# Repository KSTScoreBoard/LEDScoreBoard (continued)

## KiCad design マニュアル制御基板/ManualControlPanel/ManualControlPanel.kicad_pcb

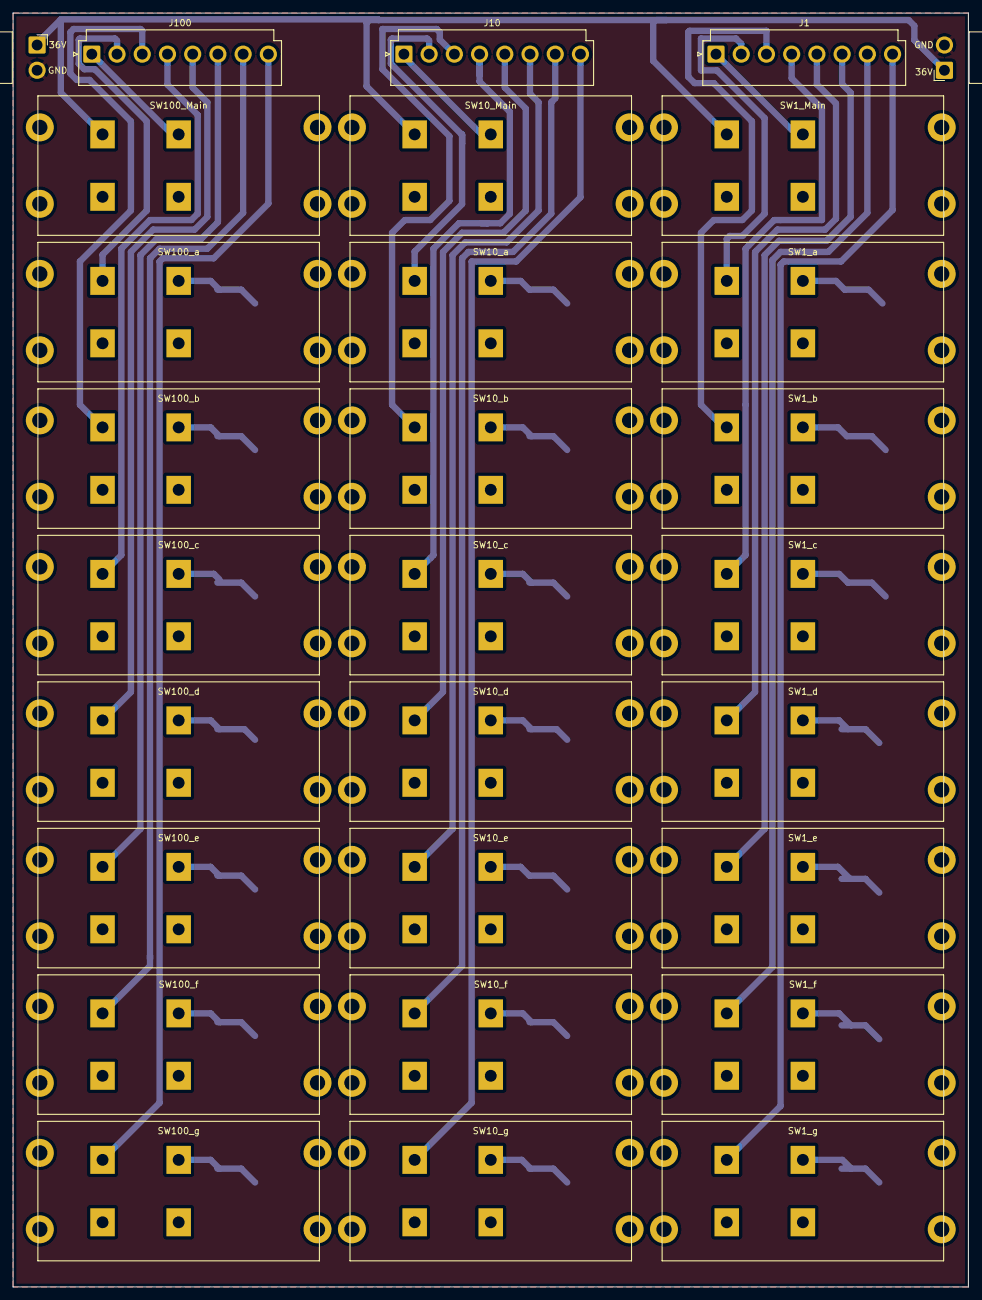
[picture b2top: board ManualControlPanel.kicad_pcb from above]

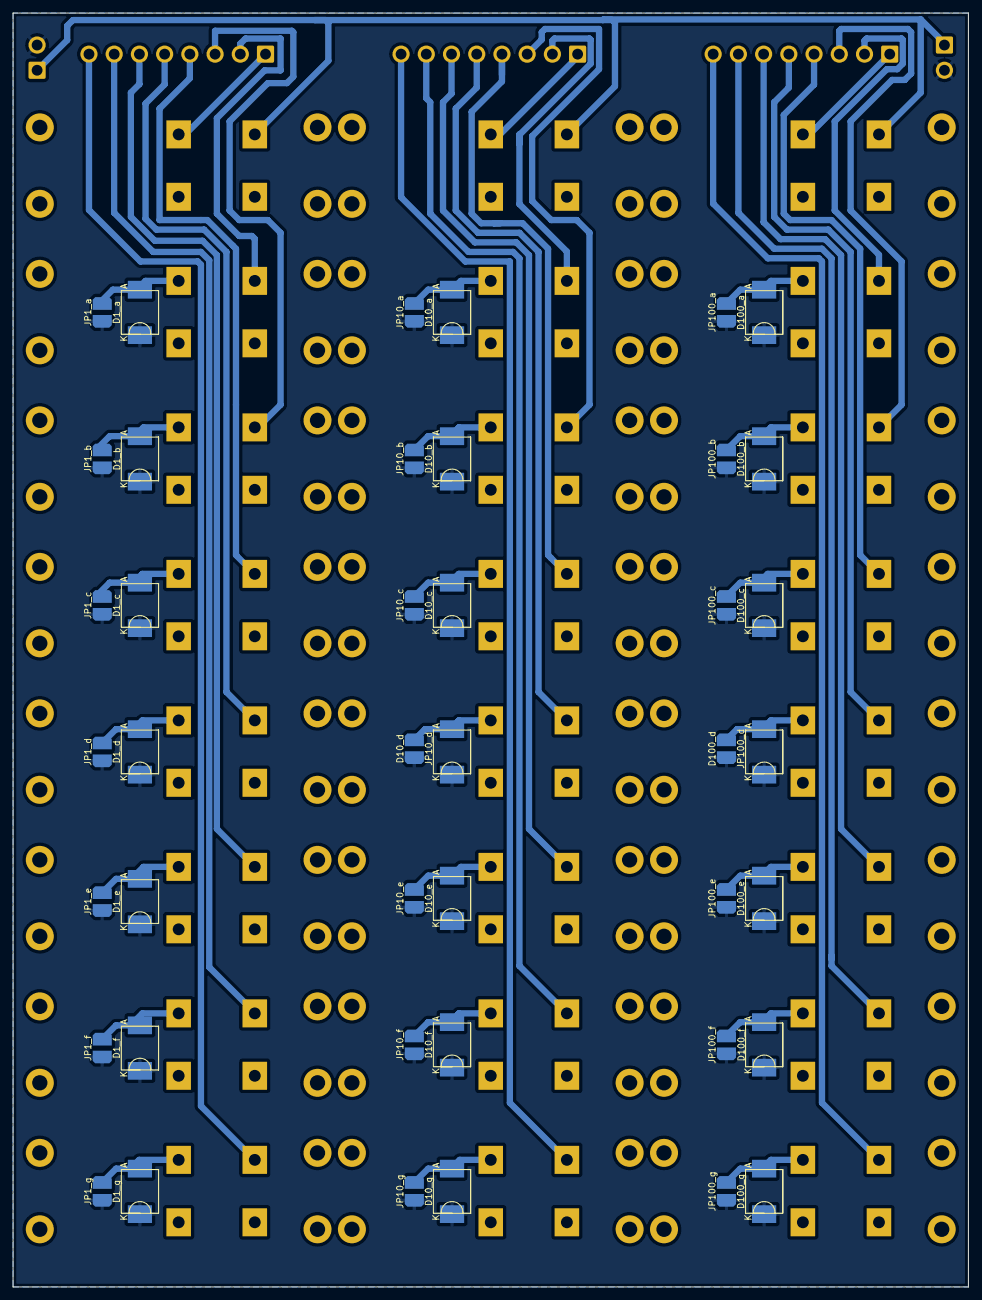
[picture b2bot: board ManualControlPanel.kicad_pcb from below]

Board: 2 copper layers, 150.0 x 200.0 mm, 71 parts (42 on the bottom side), 47 nets.

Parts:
D1_a, D1_b, D1_c, D1_d, D1_e, D1_f, D1_g, D10_a, D10_b, D10_c, D10_d, D10_e, D10_f, D10_g, D100_a, D100_b, D100_c, D100_d, D100_e, D100_f, D100_g: D; NSI50350AST3G
J1, J10, J100: Conn_01x08_Male; JST_VH_B8P-VH-B_1x08_P3.96mm_Vertical
J4, J5: Conn_01x02_Male; JST_VH_B2PS-VH_1x02_P3.96mm_Horizontal
JP1_a, JP1_b, JP1_c, JP1_d, JP1_e, JP1_f, JP1_g, JP10_a, JP10_b, JP10_c, JP10_d, JP10_e, JP10_f, JP10_g, JP100_a, JP100_b, JP100_c, JP100_d, JP100_e, JP100_f, JP100_g: SolderJumper_2_Open; junper
SW1_Main, SW1_a, SW1_b, SW1_c, SW1_d, SW1_e, SW1_f, SW1_g, SW10_Main, SW10_a, SW10_b, SW10_c, SW10_d, SW10_e, SW10_f, SW10_g, SW100_Main, SW100_a, SW100_b, SW100_c, SW100_d, SW100_e, SW100_f, SW100_g: SW_DPST; MS151S

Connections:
+36V: J4.1, J5.1, SW1_Main.1, SW10_Main.1, SW100_Main.1
GND: D1_a.1 (K), D1_b.1 (K), D1_c.1 (K), D1_d.1 (K), D1_e.1 (K), D1_f.1 (K), D1_g.1 (K), D10_a.1 (K), D10_b.1 (K), D10_c.1 (K), D10_d.1 (K), D10_e.1 (K), D10_f.1 (K), D10_g.1 (K), D100_a.1 (K), D100_b.1 (K), D100_c.1 (K), D100_d.1 (K), D100_e.1 (K), D100_f.1 (K), D100_g.1 (K), J4.2, J5.2, JP1_a.1 (A), JP1_b.1 (A), JP1_c.1 (A), JP1_d.1 (A), JP1_e.1 (A), JP1_f.1 (A), JP1_g.1 (A), JP10_a.1 (A), JP10_b.1 (A), JP10_c.1 (A), JP10_d.1 (A), JP10_e.1 (A), JP10_f.1 (A), JP10_g.1 (A), JP100_a.1 (A), JP100_b.1 (A), JP100_c.1 (A), JP100_d.1 (A), JP100_e.1 (A), JP100_f.1 (A), JP100_g.1 (A)
unnamed: D1_a.2 (A), JP1_a.2 (B), SW1_a.2
unnamed: D1_b.2 (A), JP1_b.2 (B), SW1_b.2
unnamed: D1_c.2 (A), JP1_c.2 (B), SW1_c.2
unnamed: D1_d.2 (A), JP1_d.2 (B), SW1_d.2
unnamed: D1_e.2 (A), JP1_e.2 (B), SW1_e.2
unnamed: D1_f.2 (A), JP1_f.2 (B), SW1_f.2
unnamed: D1_g.2 (A), JP1_g.2 (B), SW1_g.2
unnamed: D10_a.2 (A), JP10_a.2 (B), SW10_a.2
unnamed: D10_b.2 (A), JP10_b.2 (B), SW10_b.2
unnamed: D10_c.2 (A), JP10_c.2 (B), SW10_c.2
unnamed: D10_d.2 (A), JP10_d.2 (B), SW10_d.2
unnamed: D10_e.2 (A), JP10_e.2 (B), SW10_e.2
unnamed: D10_f.2 (A), JP10_f.2 (B), SW10_f.2
unnamed: D10_g.2 (A), JP10_g.2 (B), SW10_g.2
unnamed: D100_a.2 (A), JP100_a.2 (B), SW100_a.2
unnamed: D100_b.2 (A), JP100_b.2 (B), SW100_b.2
unnamed: D100_c.2 (A), JP100_c.2 (B), SW100_c.2
unnamed: D100_d.2 (A), JP100_d.2 (B), SW100_d.2
unnamed: D100_e.2 (A), JP100_e.2 (B), SW100_e.2
unnamed: D100_f.2 (A), JP100_f.2 (B), SW100_f.2
unnamed: D100_g.2 (A), JP100_g.2 (B), SW100_g.2
unnamed: J1.1, SW1_Main.2
unnamed: J1.2, SW1_a.1
unnamed: J1.3, SW1_b.1
unnamed: J1.4, SW1_c.1
unnamed: J1.5, SW1_d.1
unnamed: J1.6, SW1_e.1
unnamed: J1.7, SW1_f.1
unnamed: J1.8, SW1_g.1
unnamed: J10.1, SW10_Main.2
unnamed: J10.2, SW10_a.1
unnamed: J10.3, SW10_b.1
unnamed: J10.4, SW10_c.1
unnamed: J10.5, SW10_d.1
unnamed: J10.6, SW10_e.1
unnamed: J10.7, SW10_f.1
unnamed: J10.8, SW10_g.1
unnamed: J100.1, SW100_Main.2
unnamed: J100.2, SW100_a.1
unnamed: J100.3, SW100_b.1
unnamed: J100.4, SW100_c.1
unnamed: J100.5, SW100_d.1
unnamed: J100.6, SW100_e.1
unnamed: J100.7, SW100_f.1
unnamed: J100.8, SW100_g.1

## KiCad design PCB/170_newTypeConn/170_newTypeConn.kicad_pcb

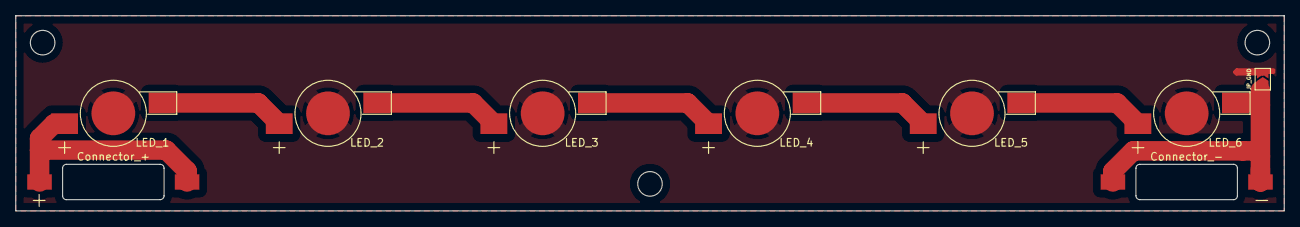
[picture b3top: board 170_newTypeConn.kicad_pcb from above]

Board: 2 copper layers, 165.1 x 25.4 mm, 9 parts (0 on the bottom side), 8 nets.

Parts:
Connector_+: Conn_01x01_Female; BJB46111
Connector_-: Conn_01x01_Female; BJB46111
JP_GND: Jumper_2_Open; SolderJumper-2_P1.3mm_Open_TrianglePad1.0x1.5mm
LED_1, LED_2, LED_3, LED_4, LED_5, LED_6: LED; LED_1W_3W_R8

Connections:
GND: Connector_-.1, JP_GND.1 (A), LED_6.1 (K)
GND1: JP_GND.2 (B), LED_1.3, LED_2.3, LED_3.3, LED_4.3, LED_5.3, LED_6.3
unnamed: LED_1.1 (K), LED_2.2 (A)
unnamed: LED_2.1 (K), LED_3.2 (A)
unnamed: LED_3.1 (K), LED_4.2 (A)
unnamed: LED_4.1 (K), LED_5.2 (A)
unnamed: LED_5.1 (K), LED_6.2 (A)
VDD: Connector_+.1, LED_1.2 (A)

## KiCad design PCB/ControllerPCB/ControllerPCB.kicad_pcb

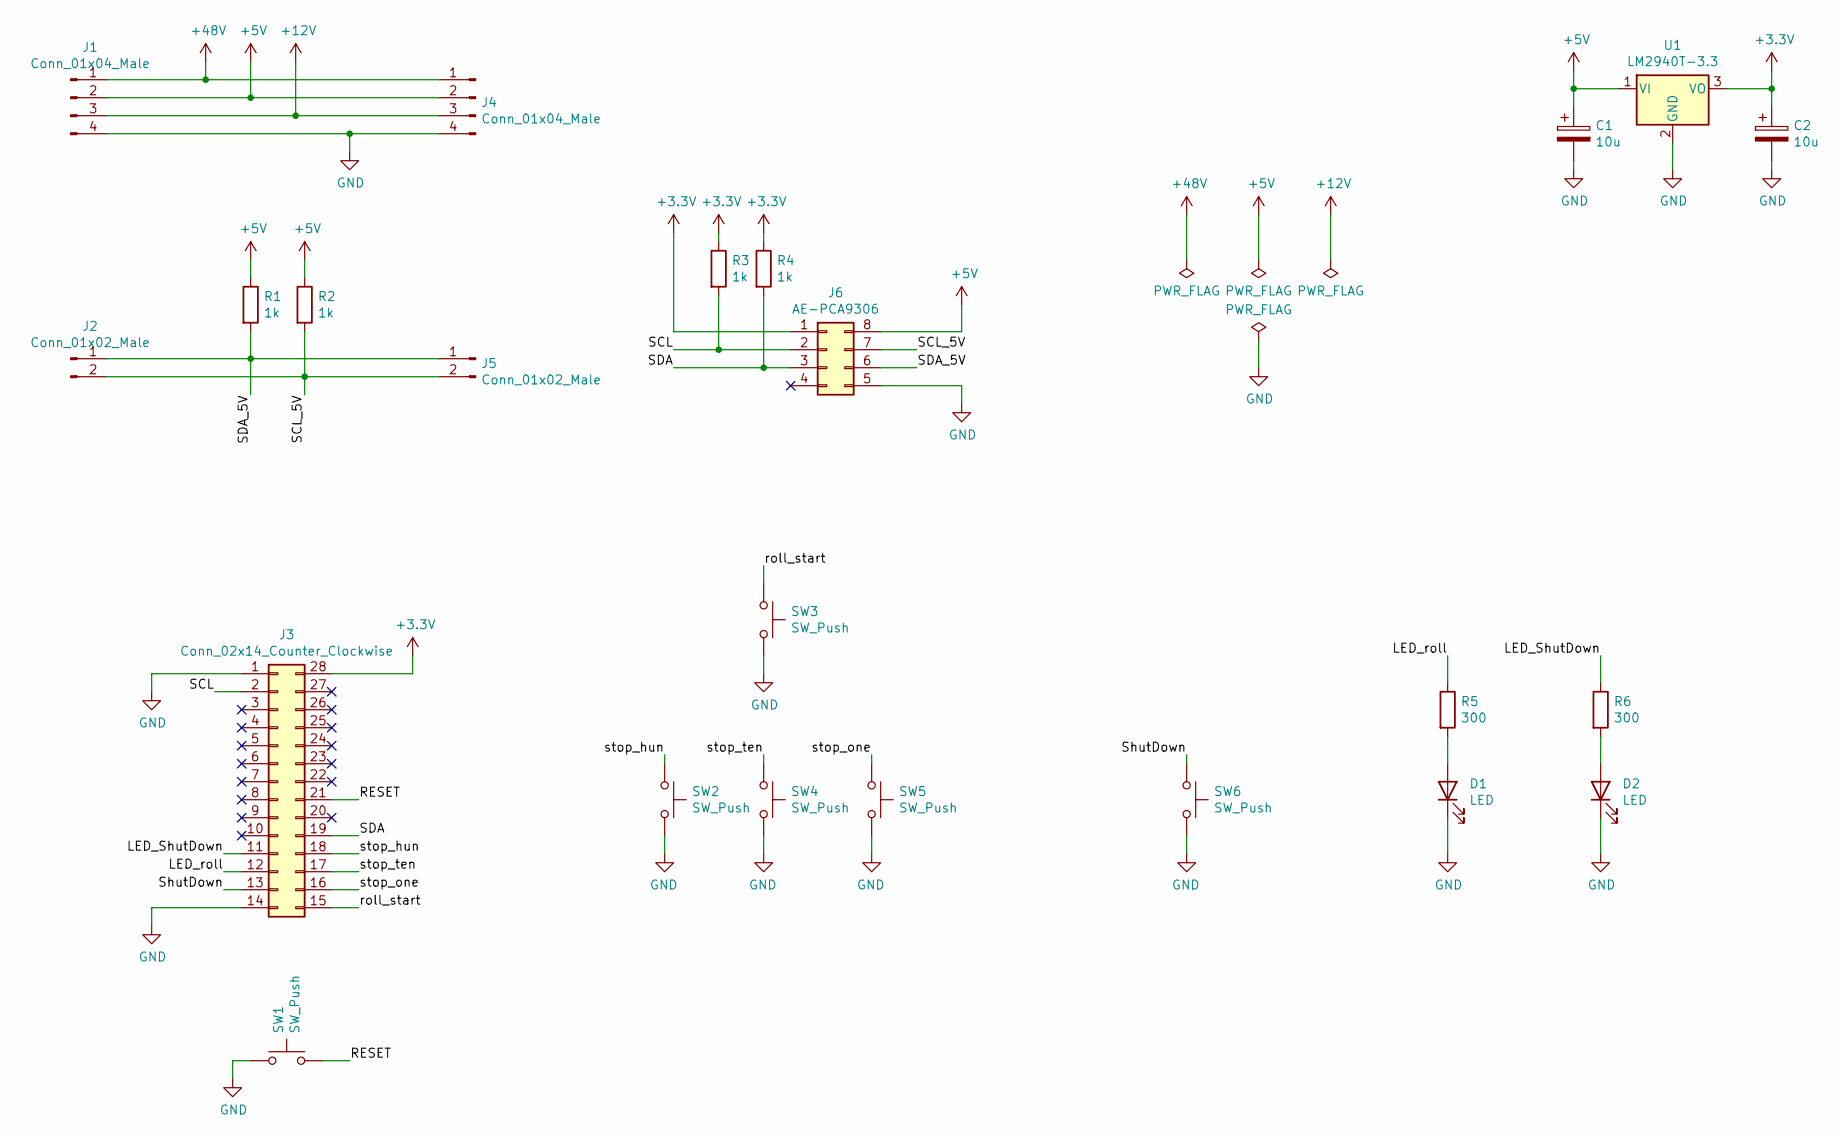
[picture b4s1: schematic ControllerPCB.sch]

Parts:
C1, C2: 10u; CP_Radial_D5.0mm_P2.00mm
D1, D2: LED; LED_0603_1608Metric
J1, J4: Conn_01x04_Male; JST_VH_B4P-VH_1x04_P3.96mm_Vertical
J2, J5: Conn_01x02_Male; JST_XH_B2B-XH-A_1x02_P2.50mm_Vertical
J3: Conn_02x14_Counter_Clockwise; DIP-28_W15.24mm
J6: AE-PCA9306; DIP-8_W7.62mm
R1, R2, R3, R4: 1k; R_0603_1608Metric
R5, R6: 300; R_0603_1608Metric
SW1, SW2, SW3, SW4, SW5, SW6: SW_Push; SW_PUSH_6mm_H5mm
U1: LM2940T-3.3; TO-220-3_Vertical

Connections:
+3V3: C2.1, J3.28, J6.1, R3.1, R4.1, U1.3 (VO)
+5V: C1.1, J1.2, J4.2, J6.8, R1.1, R2.1, U1.1 (VI)
+12V: J1.3, J4.3
+48V: J1.1, J4.1
/LED_ShutDown: J3.11, R6.1
/LED_roll: J3.12, R5.1
/RESET: J3.21, SW1.2
/SCL: J3.2, J6.2, R3.2
/SCL_5V: J2.2, J5.2, J6.7, R2.2
/SDA: J3.19, J6.3, R4.2
/SDA_5V: J2.1, J5.1, J6.6, R1.2
/ShutDown: J3.13, SW6.1
/roll_start: J3.15, SW3.1
/stop_hun: J3.18, SW2.1
/stop_one: J3.16, SW5.1
/stop_ten: J3.17, SW4.1
GND: C1.2, C2.2, D1.1 (K), D2.1 (K), J1.4, J3.1, J3.14, J4.4, J6.5, SW1.1, SW2.2, SW3.2, SW4.2, SW5.2, SW6.2, U1.2 (GND)
unnamed: D1.2 (A), R5.2
unnamed: D2.2 (A), R6.2

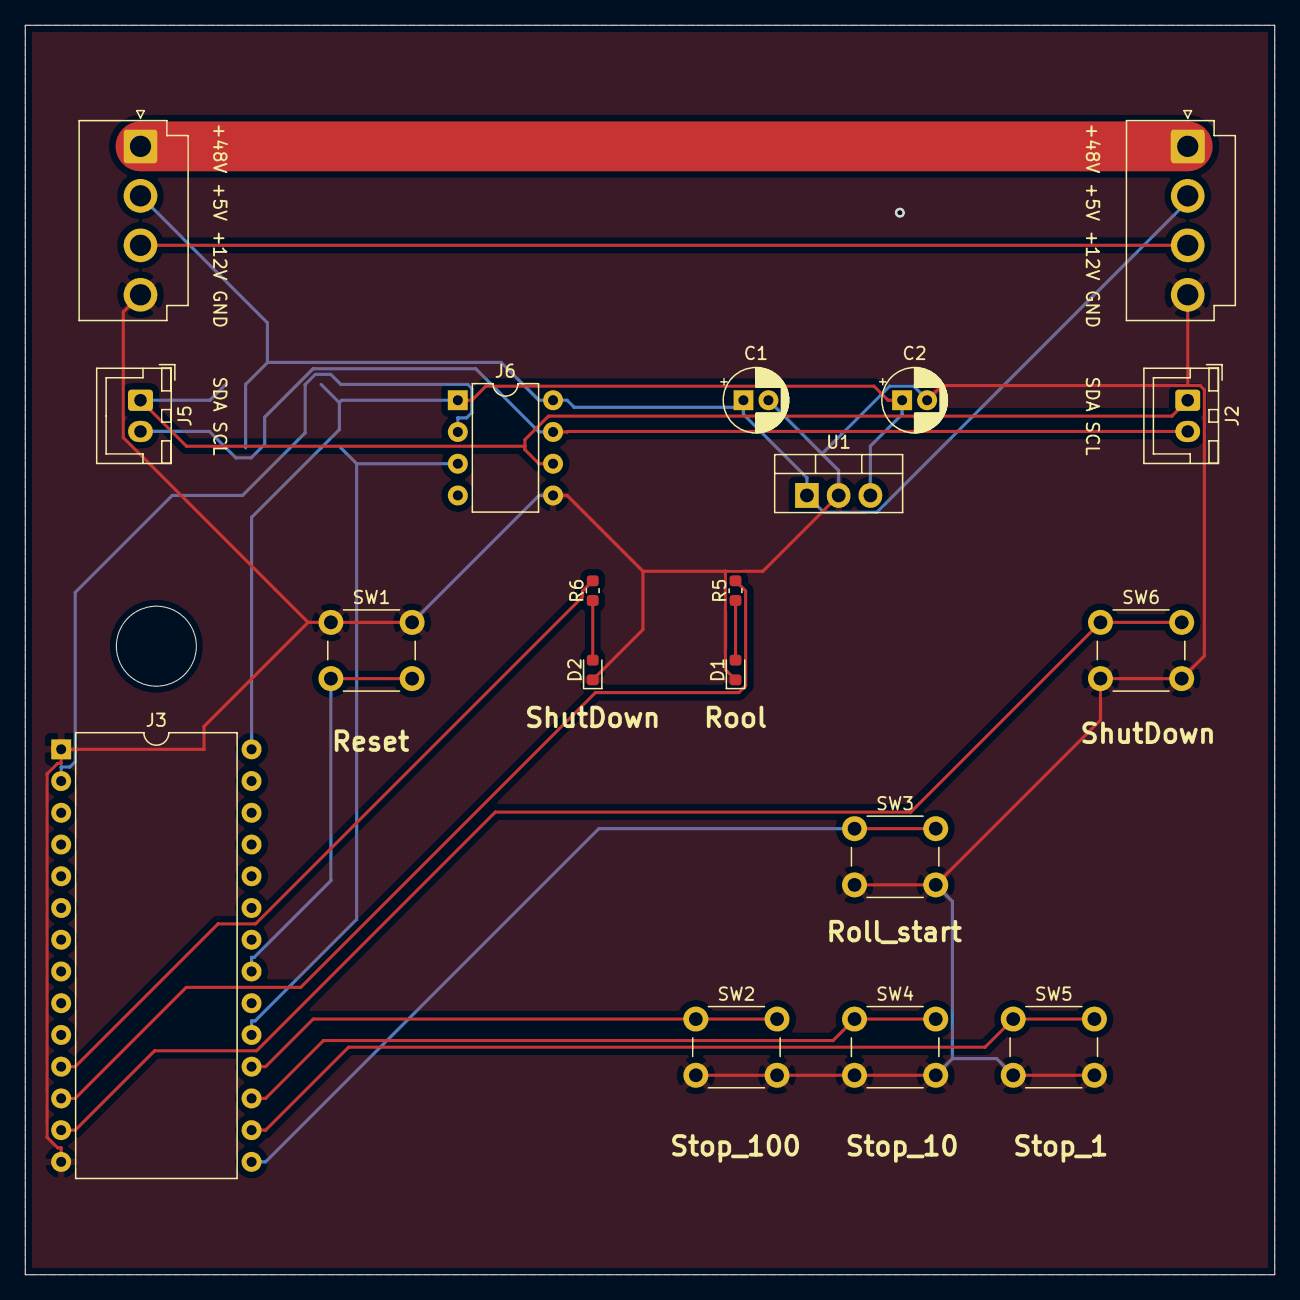
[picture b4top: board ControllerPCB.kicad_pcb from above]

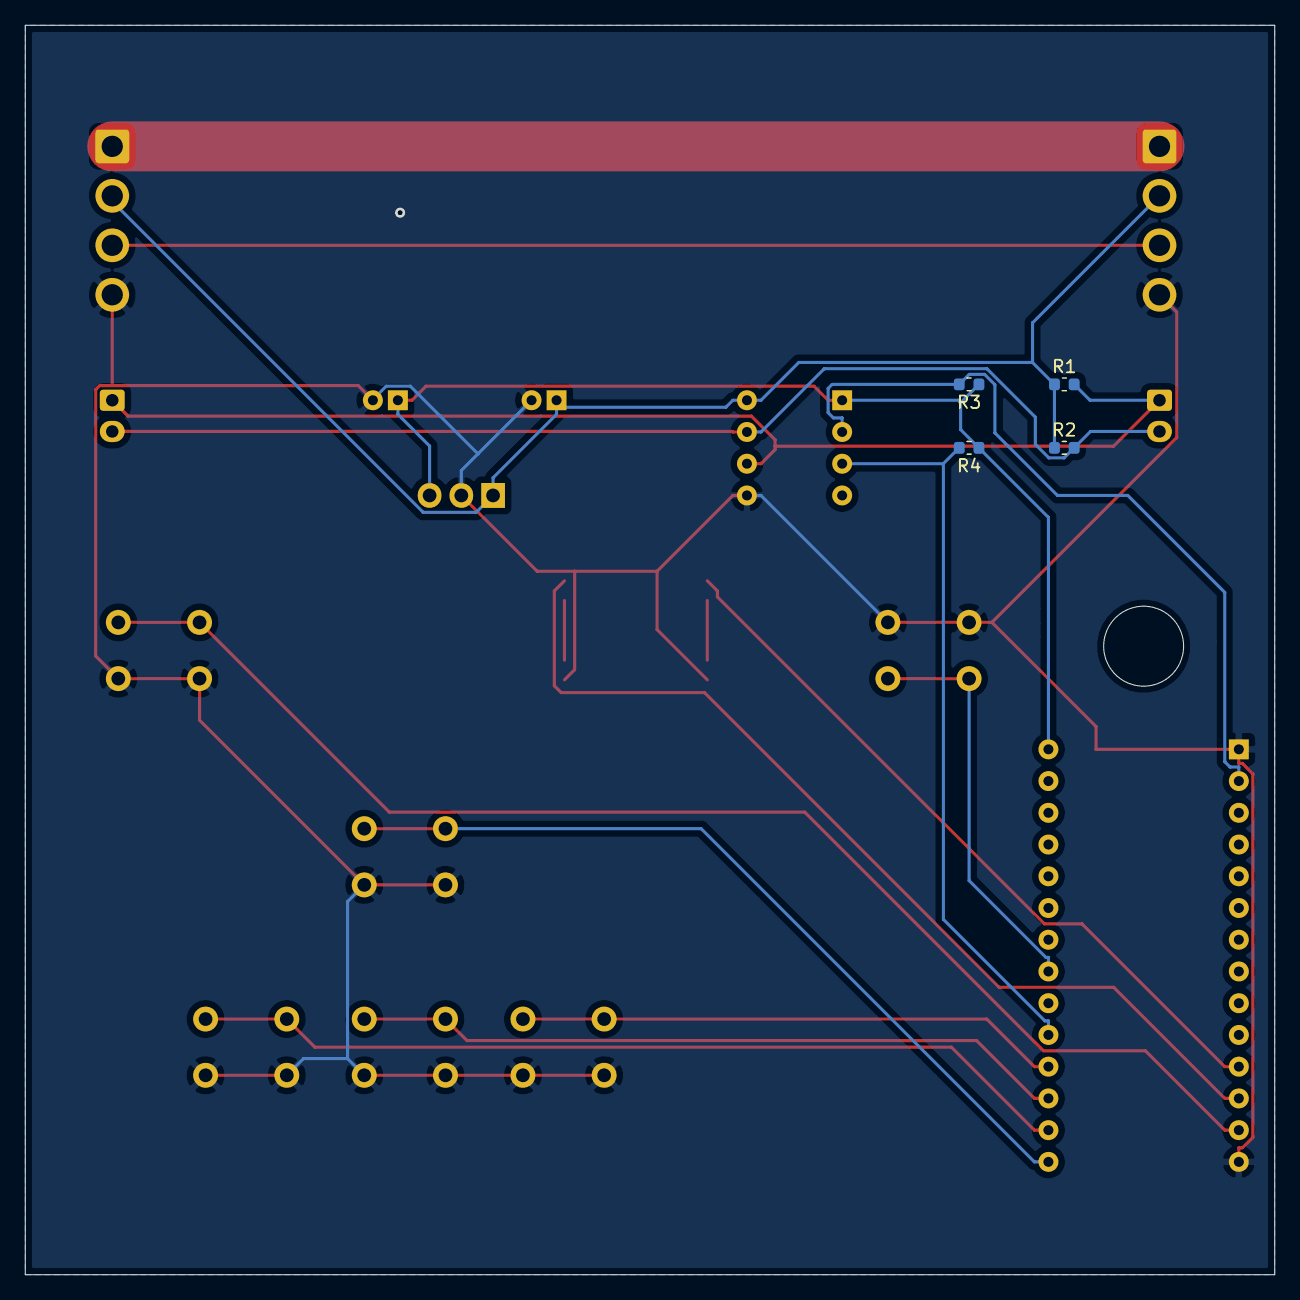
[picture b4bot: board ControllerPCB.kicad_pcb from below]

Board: 2 copper layers, 100.0 x 100.0 mm, 23 parts (4 on the bottom side), 19 nets.

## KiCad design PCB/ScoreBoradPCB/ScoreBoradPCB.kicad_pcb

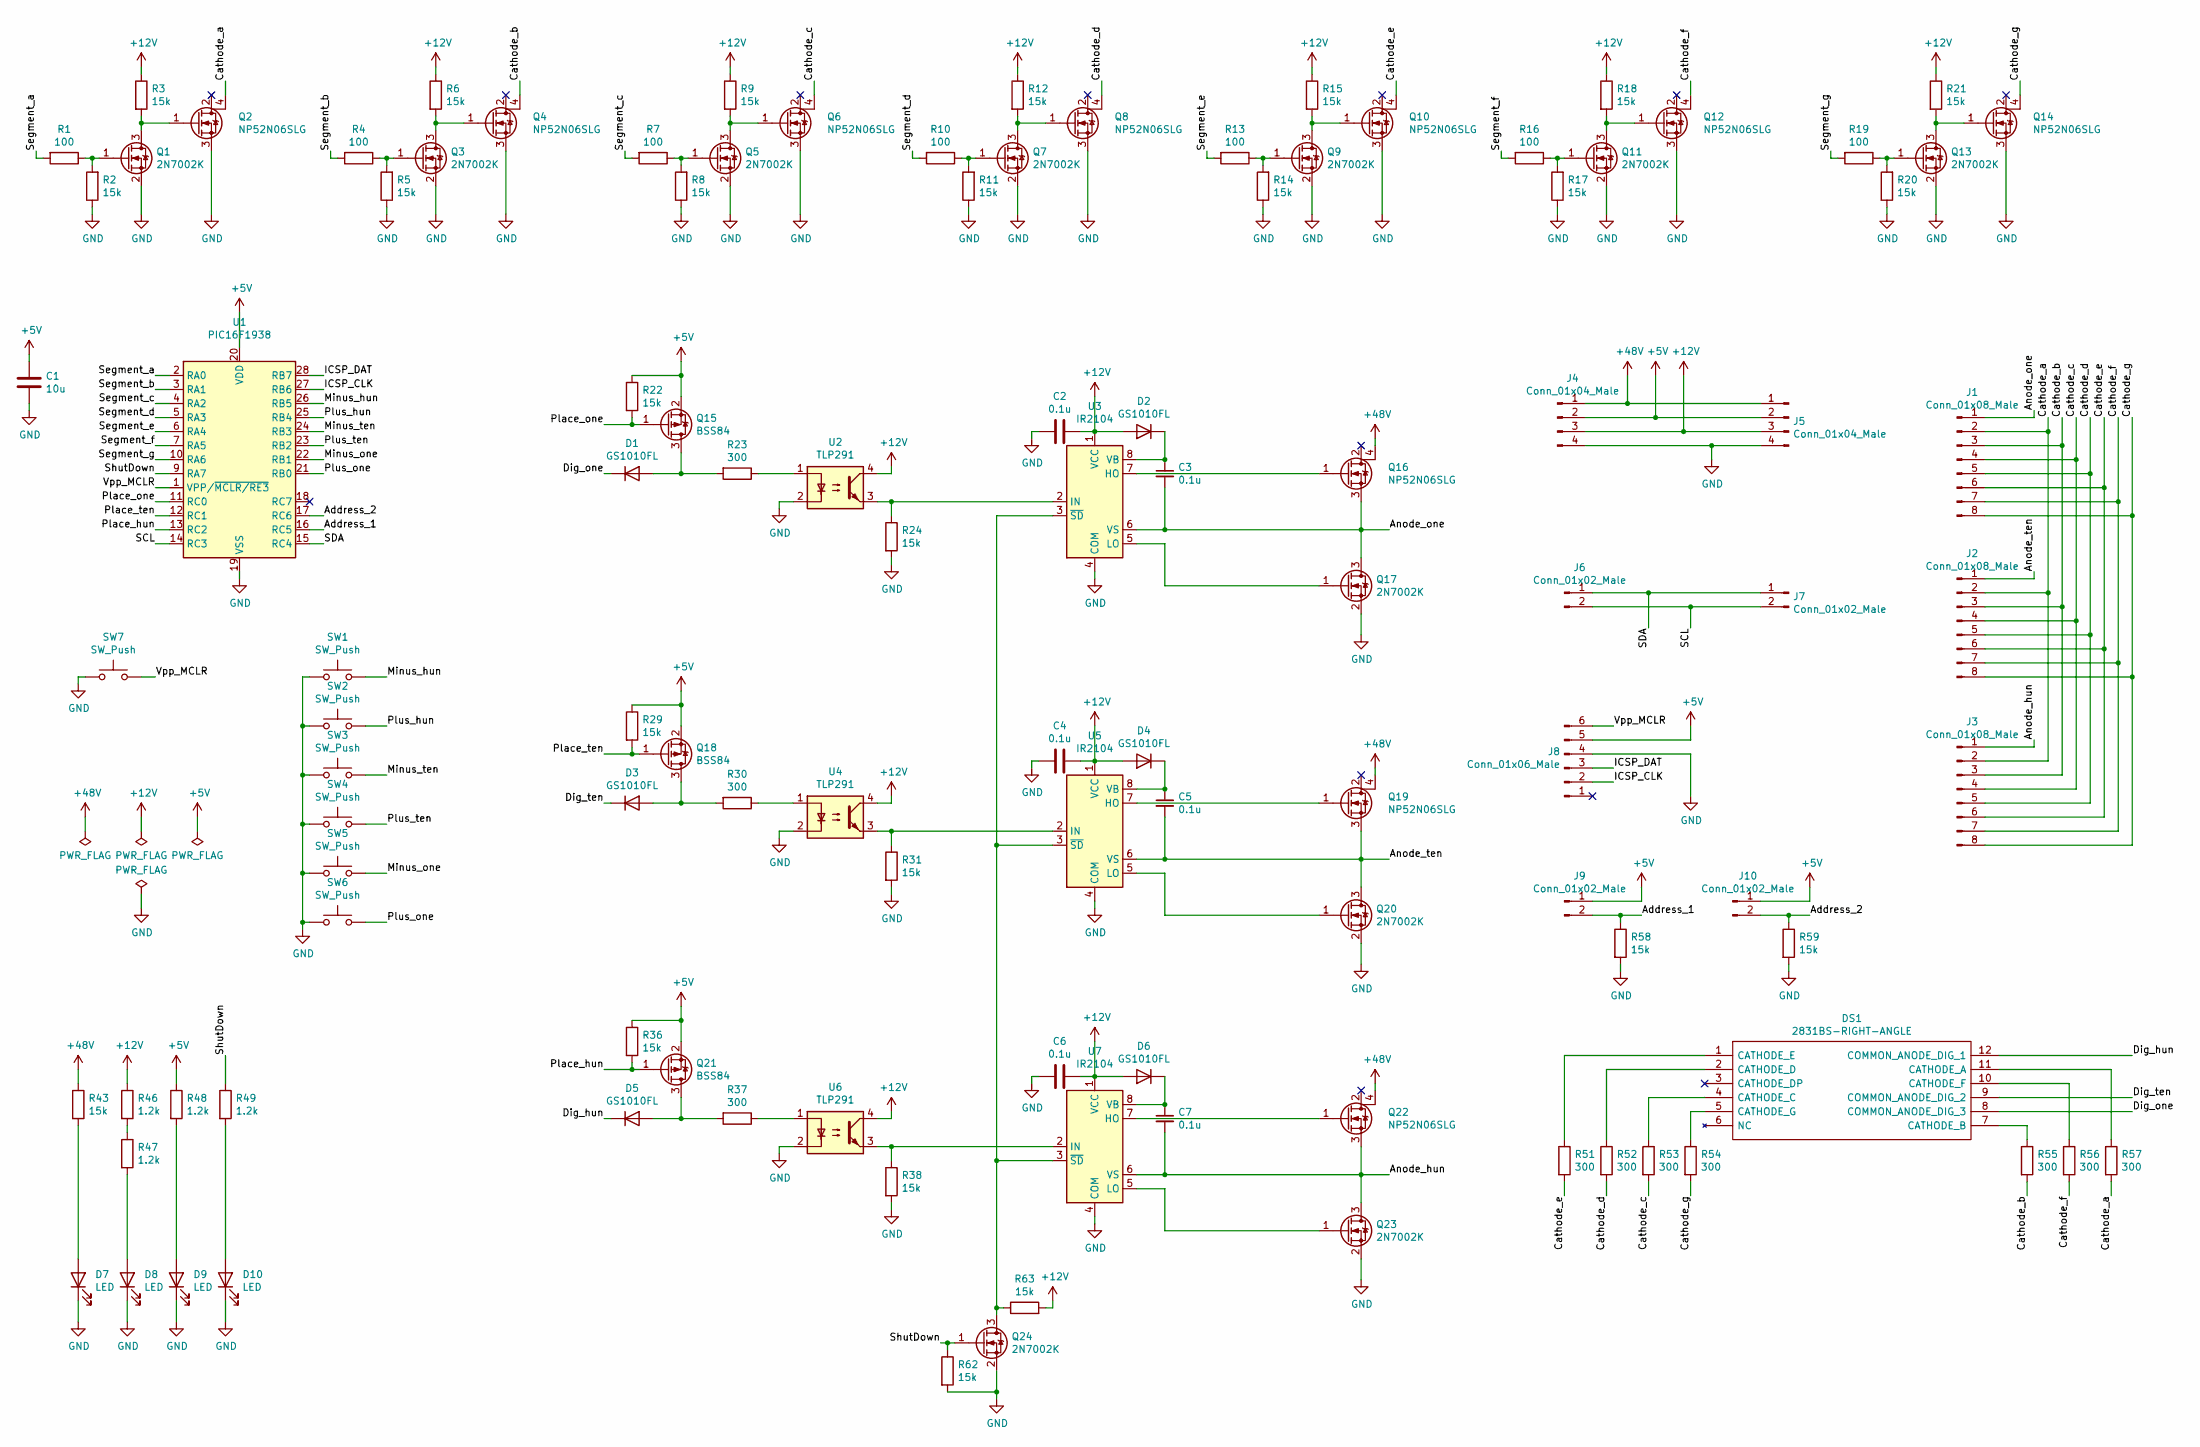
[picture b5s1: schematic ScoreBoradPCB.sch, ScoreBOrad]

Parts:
C1: 10u; C_0603_1608Metric
C2, C3, C4, C5, C6, C7: 0.1u; C_0603_1608Metric
D1, D2, D3, D4, D5, D6: GS1010FL; D_SOD-123F
D7, D8, D9, D10: LED; LED_0603_1608Metric
DS1: 2831BS-RIGHT-ANGLE; DIPS762W45P254L2253H610Q12N; Manufacturer_Part_Number 2831BS-RIGHT-ANGLE
J1, J2, J3: Conn_01x08_Male; JST_VH_B8P-VH_1x08_P3.96mm_Vertical
J4, J5: Conn_01x04_Male; JST_VH_B4P-VH_1x04_P3.96mm_Vertical
J6, J7: Conn_01x02_Male; JST_XH_B2B-XH-A_1x02_P2.50mm_Vertical
J8: Conn_01x06_Male; PinHeader_1x06_P2.54mm_Horizontal
J9, J10: Conn_01x02_Male; PinHeader_1x02_P2.54mm_Vertical
Q1, Q3, Q5, Q7, Q9, Q11, Q13, Q17, Q20, Q23, Q24: 2N7002K; SOT-23
Q2, Q4, Q6, Q8, Q10, Q12, Q14, Q16, Q19, Q22: NP52N06SLG; TO-252-3_TabPin4
Q15, Q18, Q21: BSS84; SOT-23
R1, R4, R7, R10, R13, R16, R19: 100; R_0603_1608Metric
R2, R3, R5, R6, R8, R9, R11, R12, R14, R15, R17, R18, R20, R21, R22, R24, R29, R31, R36, R38, R43, R58, R59, R62, R63: 15k; R_0603_1608Metric
R23, R30, R37, R51, R52, R53, R54, R55, R56, R57: 300; R_0603_1608Metric
R46, R47, R48, R49: 1.2k; R_0603_1608Metric
SW1, SW2, SW3, SW4, SW5, SW6, SW7: SW_Push; SW_PUSH_6mm_H5mm
U1: PIC16F1938; DIP-28_W7.62mm_Socket
U2, U4, U6: TLP291; SOIC-4_4.55x2.6mm_P1.27mm
U3, U5, U7: IR2104; SOIC-8_3.9x4.9mm_P1.27mm

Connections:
+5V: C1.1, J4.2, J5.2, J8.5, J9.1, J10.1, Q15.2 (S), Q18.2 (S), Q21.2 (S), R22.1, R29.1, R36.1, R48.1, U1.20 (VDD); also elsewhere on the board
+12V: C2.1, C4.1, C6.1, D2.2 (A), D4.2 (A), D6.2 (A), J4.3, J5.3, R3.1, R6.1, R9.1, R12.1, R15.1, R18.1, R21.1, R46.1, R63.2, U2.4, U3.1 (VCC), U4.4, U5.1 (VCC), U6.4, U7.1 (VCC)
+48V: J4.1, J5.1, Q16.4 (D), Q19.4 (D), Q22.4 (D), R43.1
/Address_1: J9.2, R58.1, U1.16 (RC5)
/Address_2: J10.2, R59.1, U1.17 (RC6)
/Anode_hun: C7.2, J3.1, Q22.3 (S), Q23.3 (D), U7.6 (VS); also elsewhere on the board
/Anode_one: C3.2, J1.1, Q16.3 (S), Q17.3 (D), U3.6 (VS); also elsewhere on the board
/Anode_ten: C5.2, J2.1, Q19.3 (S), Q20.3 (D), U5.6 (VS); also elsewhere on the board
/Cathode_a: J1.2, J2.2, J3.2, Q2.4 (D), R57.2
/Cathode_b: J1.3, J2.3, J3.3, Q4.4 (D), R55.2
/Cathode_c: J1.4, J2.4, J3.4, Q6.4 (D), R53.2
/Cathode_d: J1.5, J2.5, J3.5, Q8.4 (D), R52.2
/Cathode_e: J1.6, J2.6, J3.6, Q10.4 (D), R51.2
/Cathode_f: J1.7, J2.7, J3.7, Q12.4 (D), R56.2
/Cathode_g: J1.8, J2.8, J3.8, Q14.4 (D), R54.2
/Dig_hun: D5.1 (K), DS1.12 (COMMON_ANODE_DIG_1)
/Dig_one: D1.1 (K), DS1.8 (COMMON_ANODE_DIG_3)
/Dig_ten: D3.1 (K), DS1.9 (COMMON_ANODE_DIG_2)
/ICSP_CLK: J8.2, U1.27 (RB6)
/ICSP_DAT: J8.3, U1.28 (RB7)
/Minus_hun: SW1.2, U1.26 (RB5)
/Minus_one: SW5.2, U1.22 (RB1)
/Minus_ten: SW3.2, U1.24 (RB3)
/Place_hun: Q21.1 (G), R36.2, U1.13 (RC2)
/Place_one: Q15.1 (G), R22.2, U1.11 (RC0)
/Place_ten: Q18.1 (G), R29.2, U1.12 (RC1)
/Plus_hun: SW2.2, U1.25 (RB4)
/Plus_one: SW6.2, U1.21 (RB0)
/Plus_ten: SW4.2, U1.23 (RB2)
/SCL: J6.2, J7.2, U1.14 (RC3); also elsewhere on the board
/SDA: J6.1, J7.1, U1.15 (RC4); also elsewhere on the board
/Segment_a: R1.2, U1.2 (RA0)
/Segment_b: R4.2, U1.3 (RA1)
/Segment_c: R7.2, U1.4 (RA2)
/Segment_d: R10.2, U1.5 (RA3)
/Segment_e: R13.2, U1.6 (RA4)
/Segment_f: R16.2, U1.7 (RA5)
/Segment_g: R19.2, U1.10 (RA6)
/ShutDown: Q24.1 (G), R49.1, R62.1, U1.9 (RA7)
/Vpp_MCLR: J8.6, SW7.2, U1.1 (VPP/~MCLR/RE3)
GND: C1.2, C2.2, C4.2, C6.2, D7.1 (K), D8.1 (K), D9.1 (K), D10.1 (K), J4.4, J5.4, J8.4, Q1.2 (S), Q2.3 (S), Q3.2 (S), Q4.3 (S), Q5.2 (S), Q6.3 (S), Q7.2 (S), Q8.3 (S), Q9.2 (S), Q10.3 (S), Q11.2 (S), Q12.3 (S), Q13.2 (S), Q14.3 (S), Q17.2 (S), Q20.2 (S), Q23.2 (S), Q24.2 (S), R2.1, R5.1, R8.1, R11.1, R14.1, R17.1, R20.1, R24.2, R31.2, R38.2, R58.2, R59.2, R62.2, SW1.1, SW2.1, SW3.1, SW4.1, SW5.1, SW6.1, SW7.1, U1.8 (VSS), U1.19 (VSS), U2.2, U3.4 (COM), U4.2, U5.4 (COM), U6.2, U7.4 (COM); also elsewhere on the board
unnamed: C3.1, D2.1 (K), U3.8 (VB)
unnamed: C5.1, D4.1 (K), U5.8 (VB)
unnamed: C7.1, D6.1 (K), U7.8 (VB)
unnamed: D1.2 (A), Q15.3 (D), R23.2
unnamed: D3.2 (A), Q18.3 (D), R30.2
unnamed: D5.2 (A), Q21.3 (D), R37.2
unnamed: D8.2 (A), R47.2
unnamed: D9.2 (A), R48.2
unnamed: D10.2 (A), R49.2
unnamed: DS1.1 (CATHODE_E), R51.1
unnamed: DS1.2 (CATHODE_D), R52.1
unnamed: DS1.4 (CATHODE_C), R53.1
unnamed: DS1.5 (CATHODE_G), R54.1
unnamed: DS1.7 (CATHODE_B), R55.1
unnamed: DS1.10 (CATHODE_F), R56.1
unnamed: DS1.11 (CATHODE_A), R57.1
unnamed: Q1.1 (G), R1.1, R2.2
unnamed: Q1.3 (D), Q2.1 (G), R3.2
unnamed: Q3.1 (G), R4.1, R5.2
unnamed: Q3.3 (D), Q4.1 (G), R6.2
unnamed: Q5.1 (G), R7.1, R8.2
unnamed: Q5.3 (D), Q6.1 (G), R9.2
unnamed: Q7.1 (G), R10.1, R11.2
unnamed: Q7.3 (D), Q8.1 (G), R12.2
unnamed: Q9.1 (G), R13.1, R14.2
unnamed: Q9.3 (D), Q10.1 (G), R15.2
unnamed: Q11.1 (G), R16.1, R17.2
unnamed: Q11.3 (D), Q12.1 (G), R18.2
unnamed: Q13.1 (G), R19.1, R20.2
unnamed: Q13.3 (D), Q14.1 (G), R21.2
unnamed 81: Q16.1 (G), U3.7 (HO); also elsewhere on the board
unnamed 83: Q17.1 (G), U3.5 (LO); also elsewhere on the board
unnamed 84: Q19.1 (G), U5.7 (HO); also elsewhere on the board
unnamed 86: Q20.1 (G), U5.5 (LO); also elsewhere on the board
unnamed 87: Q22.1 (G), U7.7 (HO); also elsewhere on the board
unnamed 89: Q23.1 (G), U7.5 (LO); also elsewhere on the board
unnamed: Q24.3 (D), R63.1, U3.3 (~SD), U5.3 (~SD), U7.3 (~SD)
unnamed: R23.1, U2.1
unnamed: R24.1, U2.3, U3.2 (IN)
unnamed: R30.1, U4.1
unnamed: R31.1, U4.3, U5.2 (IN)
unnamed: R37.1, U6.1
unnamed: R38.1, U6.3, U7.2 (IN)
unnamed: R46.2, R47.1

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
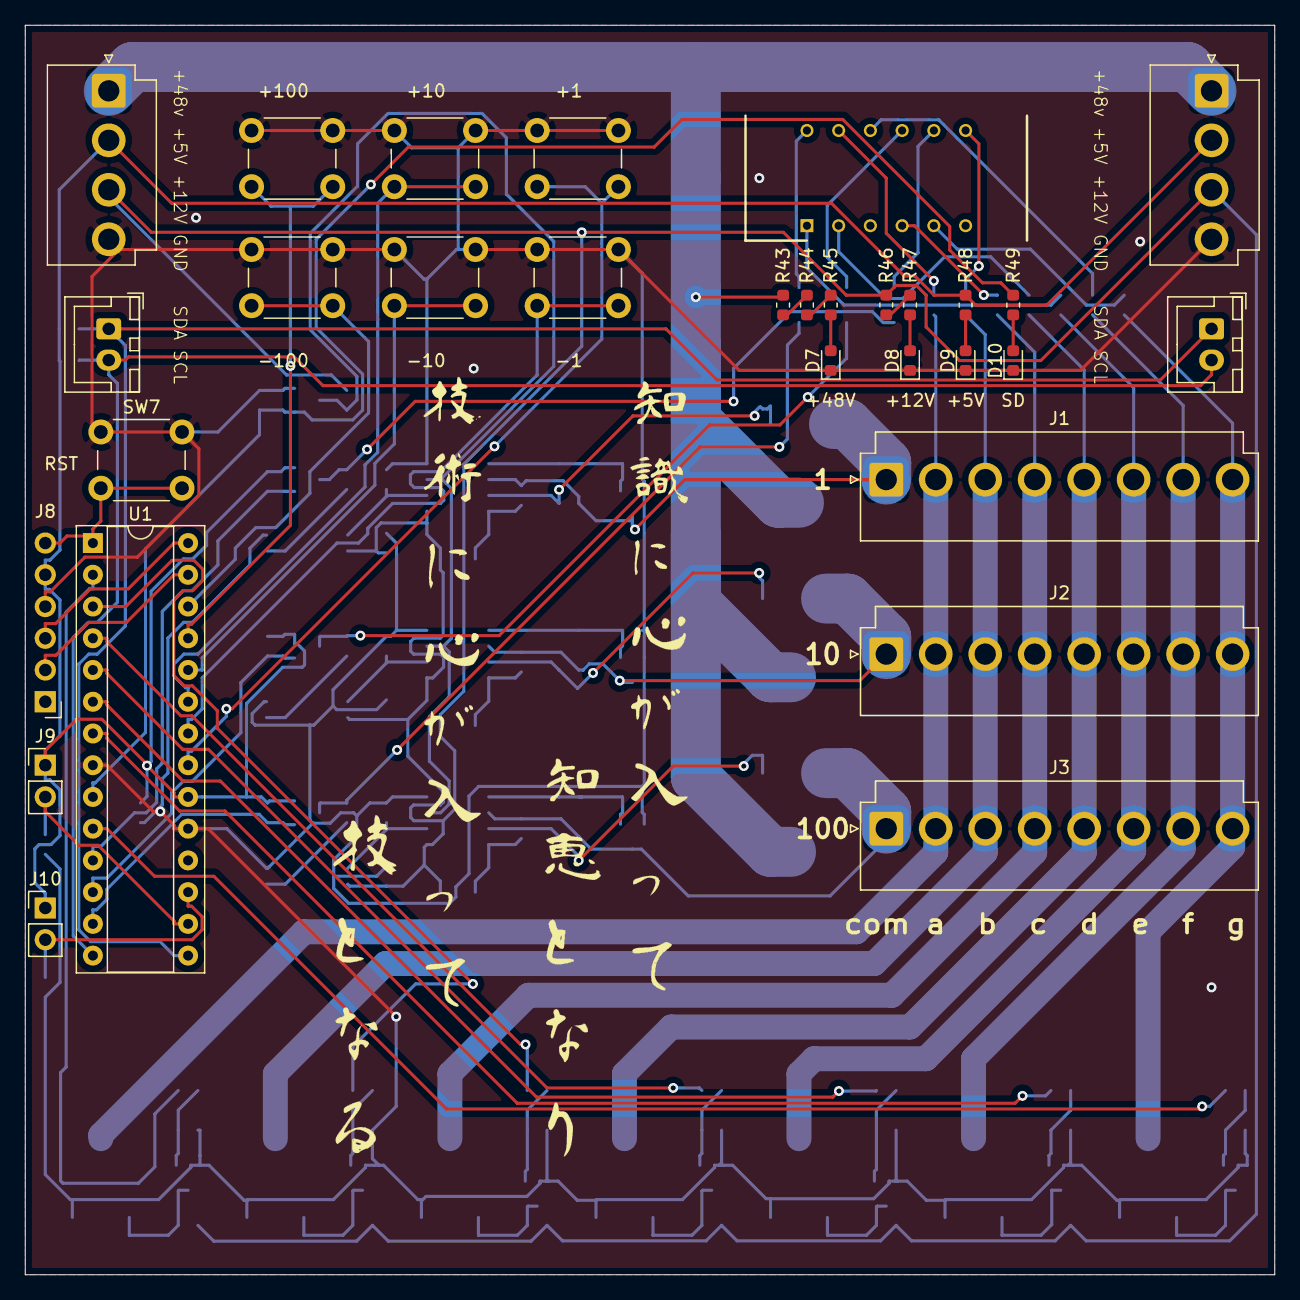
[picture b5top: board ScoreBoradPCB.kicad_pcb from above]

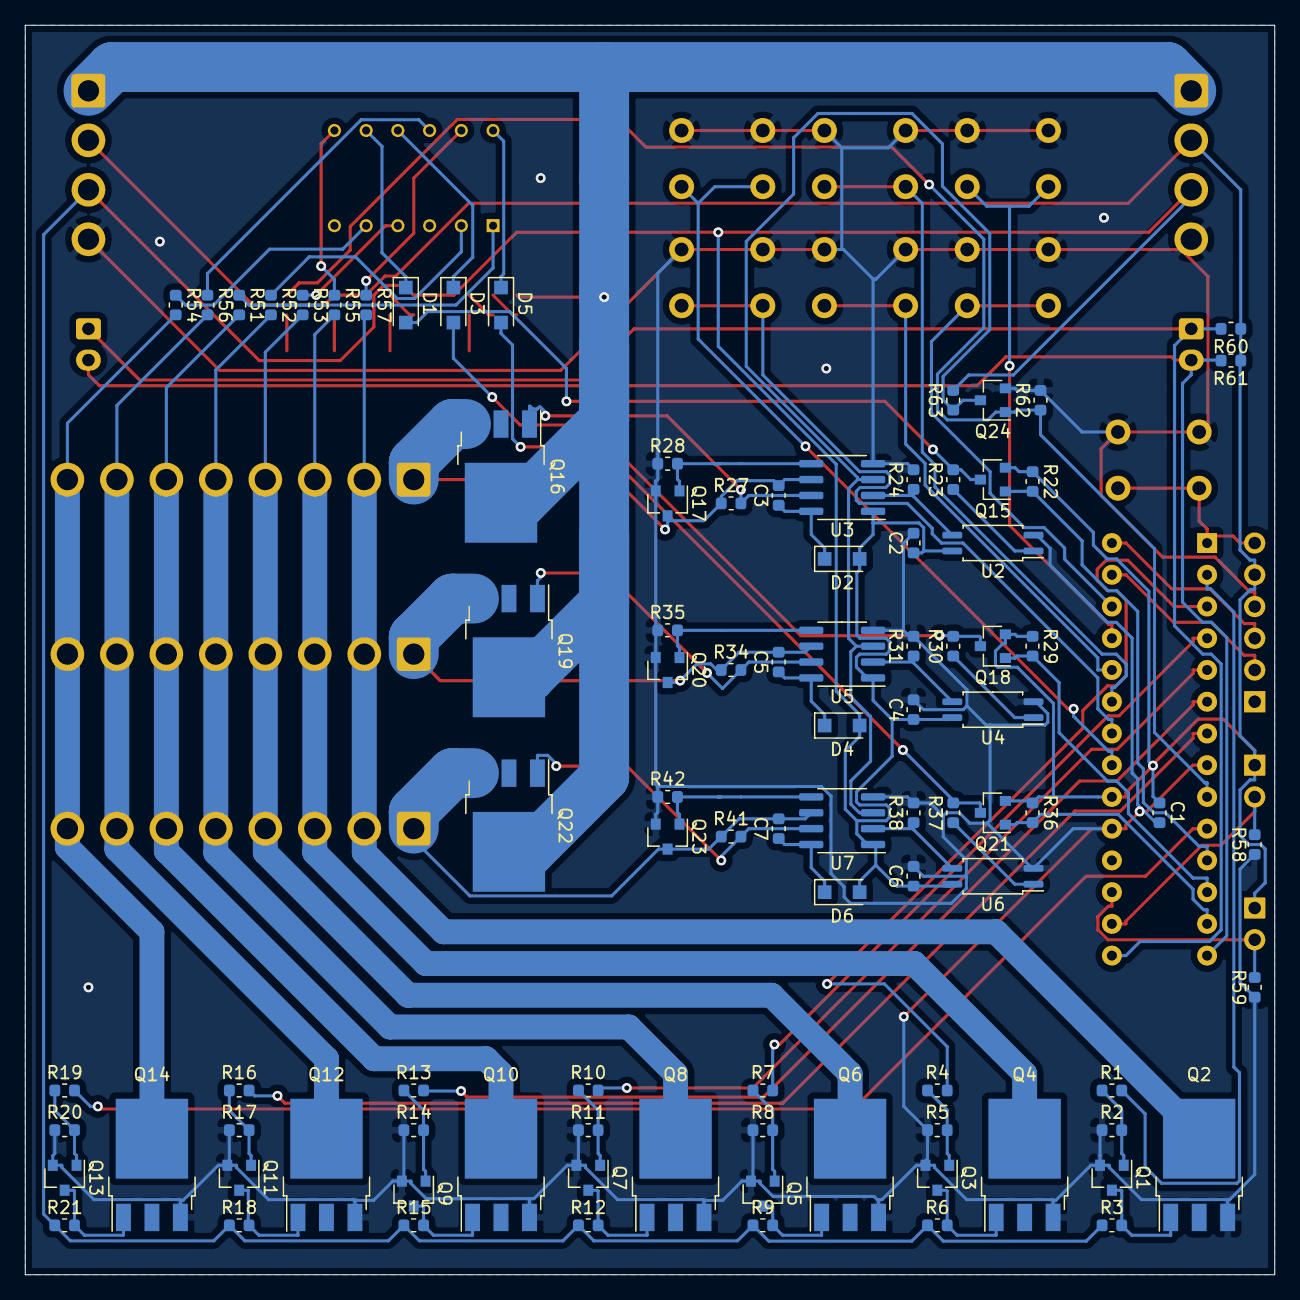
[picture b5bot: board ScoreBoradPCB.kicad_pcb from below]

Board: 2 copper layers, 100.0 x 100.0 mm, 122 parts (92 on the bottom side), 88 nets.

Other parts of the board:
R27, R28, R34, R35, R41, R42: 15k; R_0603_1608Metric
R44, R45, R60, R61: 1k; R_0603_1608Metric

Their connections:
+5V: R60.1, R61.1; also elsewhere on the board
/Anode_hun: R41.1; also elsewhere on the board
/Anode_one: R27.1; also elsewhere on the board
/Anode_ten: R34.1; also elsewhere on the board
/SCL: R61.2; also elsewhere on the board
/SDA: R60.2; also elsewhere on the board
GND: R28.1, R35.1, R42.1; also elsewhere on the board
unnamed 81: R27.2; also elsewhere on the board
unnamed 83: R28.2; also elsewhere on the board
unnamed 84: R34.2; also elsewhere on the board
unnamed 86: R35.2; also elsewhere on the board
unnamed 87: R41.2; also elsewhere on the board
unnamed 89: R42.2; also elsewhere on the board
unnamed: R44.2, R45.1

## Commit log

2022-02-03 readme画像追加
2022-02-03 chage encode
2022-02-03 操作説明
2022-02-03 構成図追加
2022-02-03 構成図イメージ
2022-02-03 Q&A追加
2022-02-03 既存ファイル追加
2022-02-06 各部説明追加
2022-02-06 Twe-liteSTAGE削除
2022-02-06 詳細解説
2022-02-06 回路図解説追加
2023-03-03 アルミLEDボードのCADデータ追加
    機械科でレーザー加工してもらう用の2004DXF形式データも込入っています
2023-03-03 電光掲示板の放熱試験の画像を追加
2023-03-03 2023ver.に差し替え
2023-03-03 不要画像削除
2023-03-04 テストプログラム
2023-03-04 backup
2023-03-04 UARTをシリアルパーサー形式に変更
2023-03-04 通信強度表示を追加
2023-03-07 マニュアル基板ケース追加
2023-03-07 マニュアル基板のデータの追加
2023-03-08 リファクタリング
2023-03-11 twelite
2023-03-13 基板改良
2023-03-14 回路修正
    三端子レギュレータ追加
    GNDパターン修正
    currentパターン同士のクリアランスを確保
    ファン端子追加
    温度センサ追加
2023-03-15 パターン修正
    LEDドライバのパスコンを最短で配線
    LEDドライバのタブをGNDに配線
    平行な信号パターン同士の距離を開け、GNDパターンを間に追加
    直角なパターンを修正
2023-03-15 パターン修正
    シフトレジスタ信号線と平行な3.3Vラインを移動
2023-03-15 パターン修正
    3.3V系を0.4mm幅に変更
2023-03-16 シフトレジスタパターン移動
2023-03-16 スペーサ穴移動
2023-03-16 穴位置移動
2023-03-17 パターン改良
2023-03-17 VHコネクタシルク削除
2023-03-17 パターン修正
2023-03-17 製造ファイル書き出し
2023-03-17 ignore追加
2023-03-17 test
2023-03-17 キャッシュ削除
2023-03-25 id関連修正
2023-03-25 Update fp-info-cache
2023-03-26 twelite compile
2023-03-28 温度センサ追加
2023-04-15 branch change
2023-05-03 others
2023-05-04 LEDhide処理修正
2023-05-16 edit readme
2023-05-22 ケースやフックのデータを更新
    ケースやフックの強度を向上させました
